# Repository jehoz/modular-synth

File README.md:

# MK-VCO KiCad Project

This repository contains KiCad project files for an **MK-VCO** (Voltage Controlled Oscillator) electronic circuit design.

## Run a KiCad Viewer with Docker

Use the provided Dockerfile and docker-compose.yml to build and run a KiCad environment with VNC and noVNC for web-based access, based on https://hub.docker.com/r/kicad/kicad

```bash
docker-compose up --build
```

- Access the KiCad environment by opening a web browser and navigating to `http://localhost:8080` (VNC password: `kicad`)
    - right click on the desktop, open a terminal, and run:
    ```bash
    kicad /workspace/mk_vco.kicad_pro
    ```

## What is KiCad?

KiCad is free, open-source software for designing electronic circuits and printed circuit boards (PCBs). These files are **not code** in the traditional programming sense—they're design files that describe electronic circuits, components, and PCB layouts.

## File Types Explained

### Project Files (.kicad_pro)
- `mk_vco.kicad_pro` - Main project configuration file
- `mk_vco_JUST_PCB.kicad_pro` - PCB-only version project configuration
- `mk_vco_JUST_PANEL.kicad_pro` - Panel-only version project configuration

These files contain project settings, design rules, and preferences.

### Schematic Files (.kicad_sch)
- `mk_vco.kicad_sch` - Main circuit schematic
- `mk_vco_JUST_PCB.kicad_sch` - PCB-only version schematic

These files contain the electrical circuit diagrams showing how components are connected.

### PCB Layout Files (.kicad_pcb)
- `mk_vco.kicad_pcb` - Main PCB layout
- `mk_vco_JUST_PCB.kicad_pcb` - PCB-only version layout
- `mk_vco_JUST_PANEL.kicad_pcb` - Panel-only version layout

These files define the physical layout of the printed circuit board, including component placement and copper traces.

### Local Settings (.kicad_prl)
- `mk_vco.kicad_prl` - Local project settings
- `mk_vco_JUST_PCB.kicad_prl` - PCB-only local settings

These files store user-specific preferences and window positions (typically not shared in version control).

## Project Variants

This project appears to have three variants:

1. **mk_vco** - Complete project (main version)
2. **mk_vco_JUST_PCB** - PCB-only version (circuit board without panel)
3. **mk_vco_JUST_PANEL** - Panel-only version (front panel design)

## How to Open These Files

1. **Download KiCad**: Get the free software from [https://www.kicad.org/](https://www.kicad.org/)
2. **Install KiCad**: Follow the installation instructions for your operating system
3. **Open Project**: Launch KiCad and open any of the `.kicad_pro` files
4. **View Schematic**: Click "Schematic Editor" to see the circuit diagram
5. **View PCB**: Click "PCB Editor" to see the board layout

## What This Project Is

A **VCO (Voltage Controlled Oscillator)** is an electronic circuit that generates oscillating signals (waveforms) with a frequency that can be controlled by an input voltage. VCOs are commonly used in synthesizers, audio equipment, and other electronic music devices.

## File Format

KiCad files use:
- **JSON** format for project files (.kicad_pro)
- **S-expression** format for schematics (.kicad_sch) and PCB layouts (.kicad_pcb)

These are text-based formats that can be opened in any text editor, but they're best viewed and edited in KiCad.

## Contributing

To modify this project, you'll need to use KiCad's graphical interface rather than editing the files directly. The file formats are complex and contain precise coordinates, component references, and electrical connection data.

## License

[Add your license information here]

---

**Note**: If you're new to electronics design, KiCad has excellent [documentation and tutorials](https://docs.kicad.org/) to help you get started.

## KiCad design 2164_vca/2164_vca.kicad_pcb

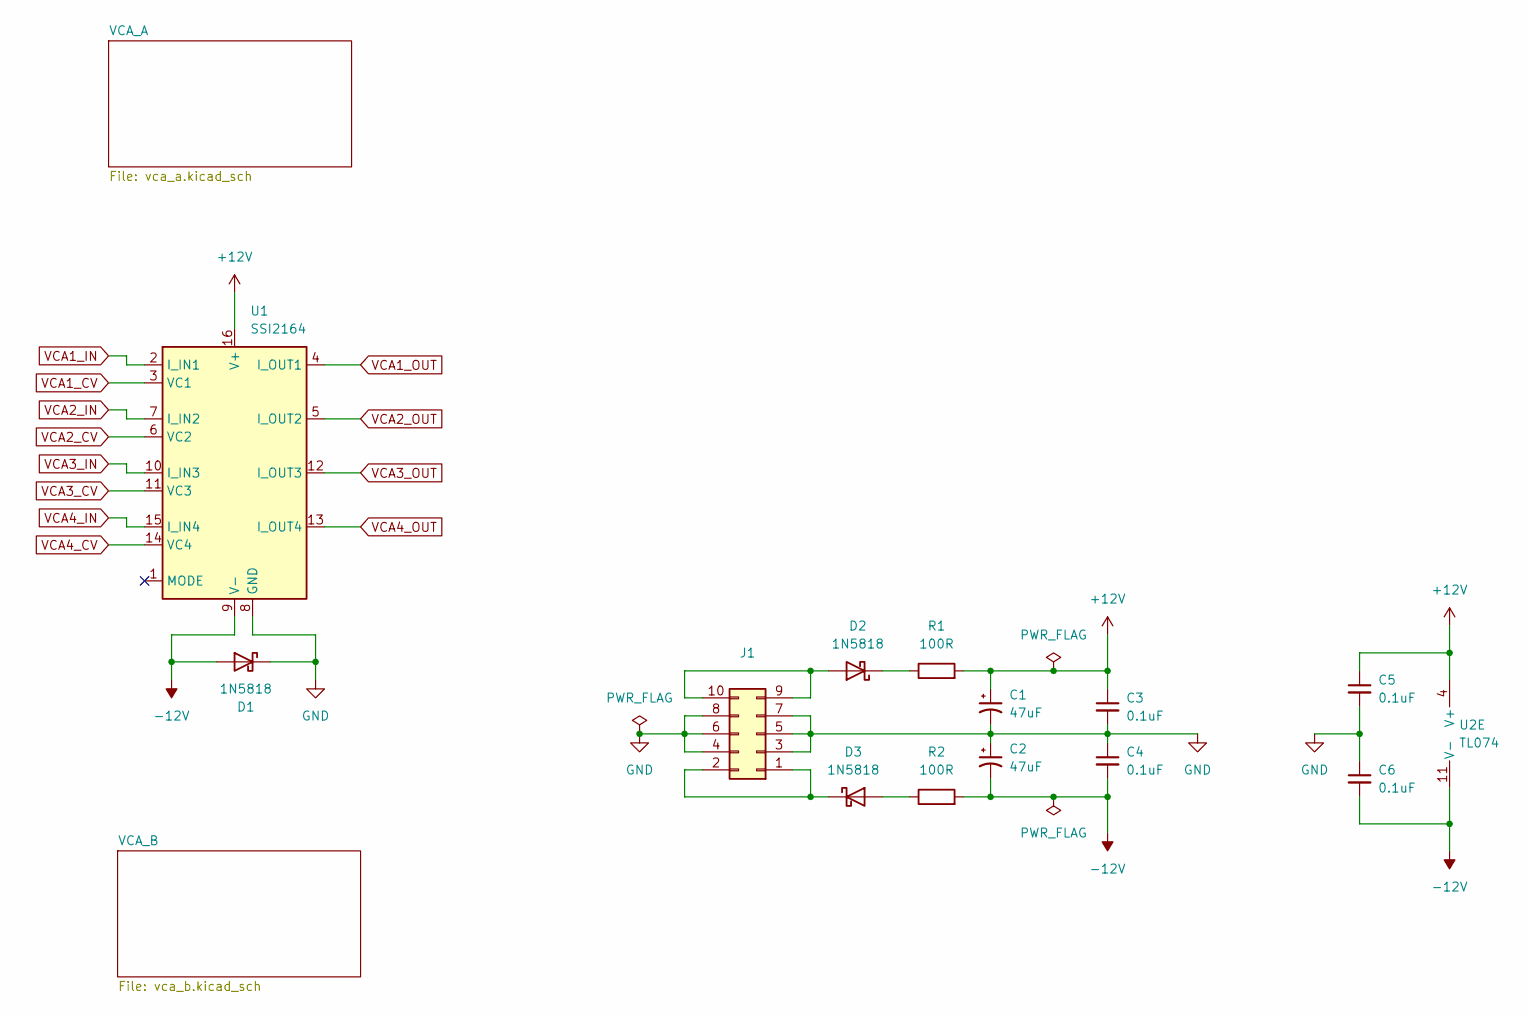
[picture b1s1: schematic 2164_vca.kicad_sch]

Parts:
C1, C2: 47uF; CP_Radial_D6.3mm_P2.50mm
C3, C4, C5, C6: 0.1uF; C_Rect_L7.2mm_W2.5mm_P5.00mm_FKS2_FKP2_MKS2_MKP2
D1, D2, D3: 1N5818; D_DO-41_SOD81_P10.16mm_Horizontal
J1: Power Connector; IDC-Header_2x05_P2.54mm_Vertical
R1, R2: 100R; R_Axial_DIN0207_L6.3mm_D2.5mm_P10.16mm_Horizontal
U1: SSI2164; DIP-16_W7.62mm_Socket
U2: TL074; DIP-14_W7.62mm_Socket

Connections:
+12V: C1.1, C3.1, C5.1, R1.2, U1.16 (V+), U2.4 (V+); also elsewhere on the board
-12V: C2.2, C4.2, C6.2, D1.2 (A), R2.2, U1.9 (V-), U2.11 (V-); also elsewhere on the board
GND: C1.2, C2.1, C3.2, C4.1, C5.2, C6.1, D1.1 (K), J1.3, J1.4, J1.5, J1.6, J1.7, J1.8, U1.8 (GND); also elsewhere on the board
unnamed: D2.2 (A), J1.9, J1.10
unnamed: D2.1 (K), R1.1
unnamed: D3.2 (A), R2.1
unnamed: D3.1 (K), J1.1, J1.2
VCA1_CV: U1.3 (VC1); also elsewhere on the board
VCA1_IN: U1.2 (I_IN1); also elsewhere on the board
VCA1_OUT: U1.4 (I_OUT1); also elsewhere on the board
VCA2_CV: U1.6 (VC2); also elsewhere on the board
VCA2_IN: U1.7 (I_IN2); also elsewhere on the board
VCA2_OUT: U1.5 (I_OUT2); also elsewhere on the board
VCA3_CV: U1.11 (VC3); also elsewhere on the board
VCA3_IN: U1.10 (I_IN3); also elsewhere on the board
VCA3_OUT: U1.12 (I_OUT3); also elsewhere on the board
VCA4_CV: U1.14 (VC4); also elsewhere on the board
VCA4_IN: U1.15 (I_IN4); also elsewhere on the board
VCA4_OUT: U1.13 (I_OUT4); also elsewhere on the board

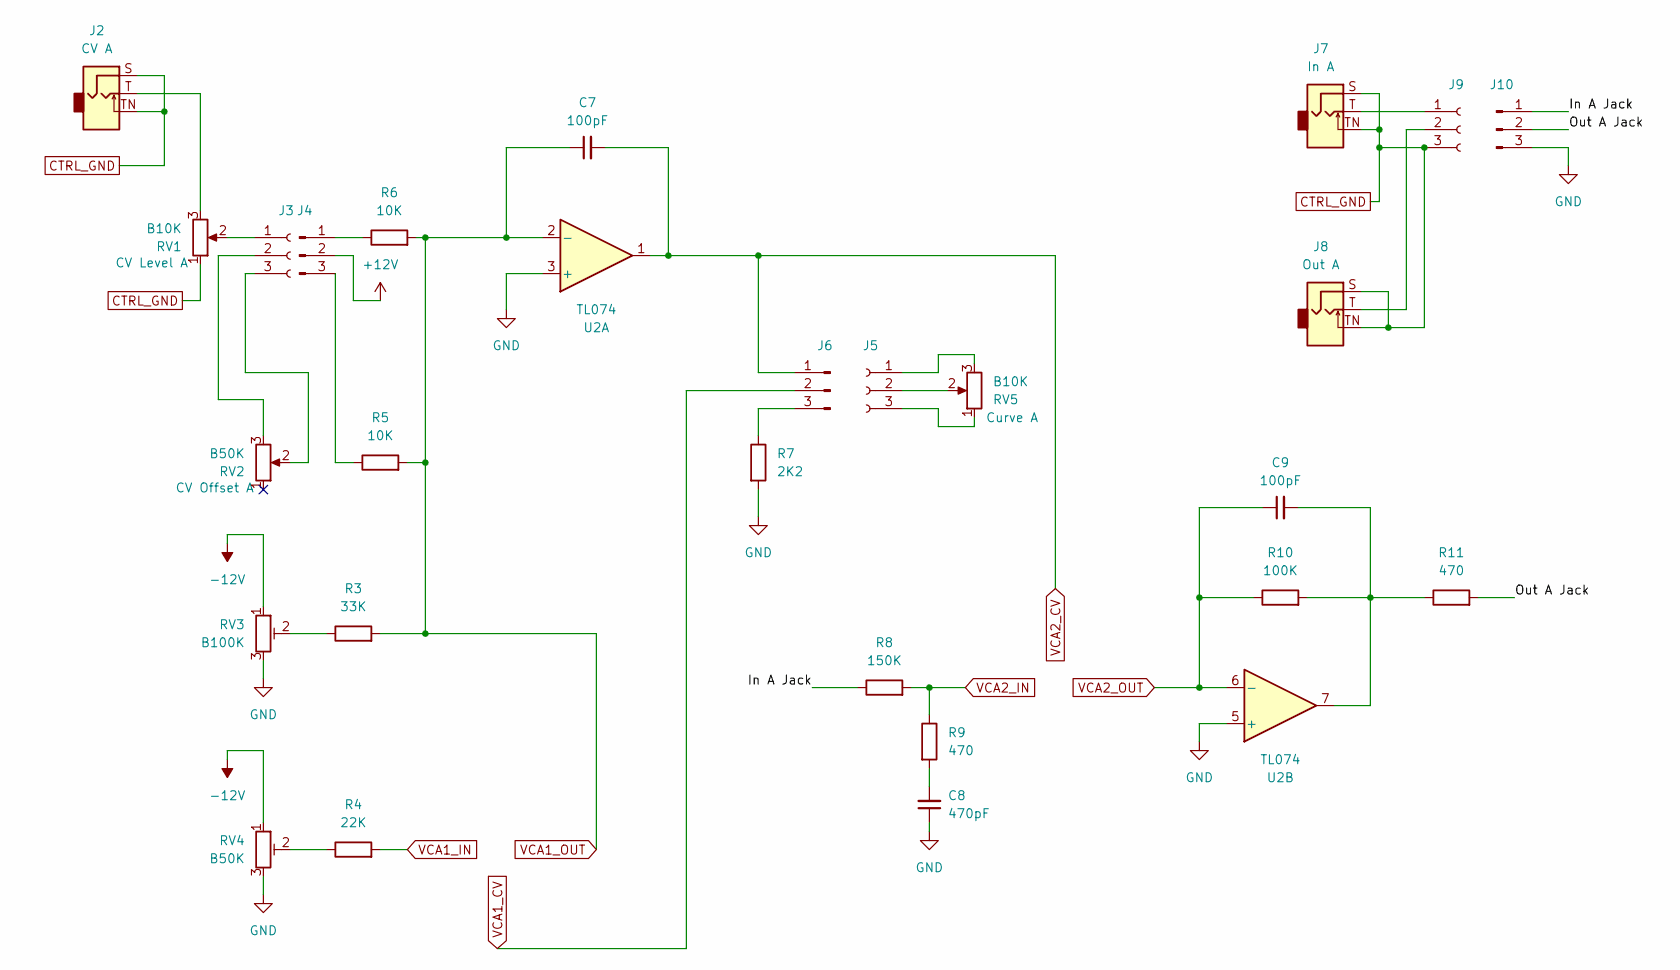
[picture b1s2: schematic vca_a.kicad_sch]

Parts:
C7, C9: 100pF; C_Rect_L7.2mm_W2.5mm_P5.00mm_FKS2_FKP2_MKS2_MKP2
C8: 470pF; C_Rect_L7.2mm_W2.5mm_P5.00mm_FKS2_FKP2_MKS2_MKP2
J2: CV A; Jack_3.5mm_QingPu_WQP-PJ398SM_Vertical_CircularHoles
J3, J5, J9: To J3; PinSocket_1x03_P2.54mm_Vertical
J4, J6, J10: Conn_01x03_Pin; PinHeader_1x03_P2.54mm_Vertical
J7: In A; Jack_3.5mm_QingPu_WQP-PJ398SM_Vertical_CircularHoles
J8: Out A; Jack_3.5mm_QingPu_WQP-PJ398SM_Vertical_CircularHoles
R3: 33K; R_Axial_DIN0207_L6.3mm_D2.5mm_P10.16mm_Horizontal
R4: 22K; R_Axial_DIN0207_L6.3mm_D2.5mm_P10.16mm_Horizontal
R5, R6: 10K; R_Axial_DIN0207_L6.3mm_D2.5mm_P10.16mm_Horizontal
R7: 2K2; R_Axial_DIN0207_L6.3mm_D2.5mm_P10.16mm_Horizontal
R8: 150K; R_Axial_DIN0207_L6.3mm_D2.5mm_P10.16mm_Horizontal
R9, R11: 470; R_Axial_DIN0207_L6.3mm_D2.5mm_P10.16mm_Horizontal
R10: 100K; R_Axial_DIN0207_L6.3mm_D2.5mm_P10.16mm_Horizontal
RV1, RV5: B10K; Potentiometer_Alpha_RD901F-40-00D_Single_Vertical_CircularH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
RV2: B50K; Potentiometer_Alpha_RD901F-40-00D_Single_Vertical_CircularH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
RV3: B100K; Potentiometer_Runtron_RM-065_Vertical
RV4: B50K; Potentiometer_Runtron_RM-065_Vertical
U2: TL074; DIP-14_W7.62mm_Socket

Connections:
+12V: J4.2; also elsewhere on the board
-12V: RV3.1, RV4.1; also elsewhere on the board
/VCA_A/In A Jack: J10.1, R8.1
/VCA_A/Out A Jack: J10.2, R11.2
CTRL_GND: J2.S, J2.TN, J7.S, J7.TN, J8.S, J8.TN, J9.3, RV1.1; also elsewhere on the board
GND: C8.1, J10.3, R7.2, RV3.3, RV4.3, U2.3 (+), U2.5 (+); also elsewhere on the board
unnamed: C8.2, R9.2
unnamed: C9.2, R10.2, R11.1, U2.7
unnamed: J2.T, RV1.3
unnamed: J3.1, RV1.2
unnamed: J3.2, RV2.3
unnamed: J3.3, RV2.2
unnamed: J4.1, R6.1
unnamed: J4.3, R5.1
unnamed: J5.1, RV5.3
unnamed: J5.2, RV5.2
unnamed: J5.3, RV5.1
unnamed: J6.3, R7.1
unnamed: J7.T, J9.1
unnamed: J8.T, J9.2
unnamed: R3.1, RV3.2
unnamed: R4.1, RV4.2
VCA1_CV: J6.2; also elsewhere on the board
VCA1_IN: R4.2; also elsewhere on the board
VCA1_OUT: C7.1, R3.2, R5.2, R6.2, U2.2 (-); also elsewhere on the board
VCA2_CV: C7.2, J6.1, U2.1; also elsewhere on the board
VCA2_IN: R8.2, R9.1; also elsewhere on the board
VCA2_OUT: C9.1, R10.1, U2.6 (-); also elsewhere on the board

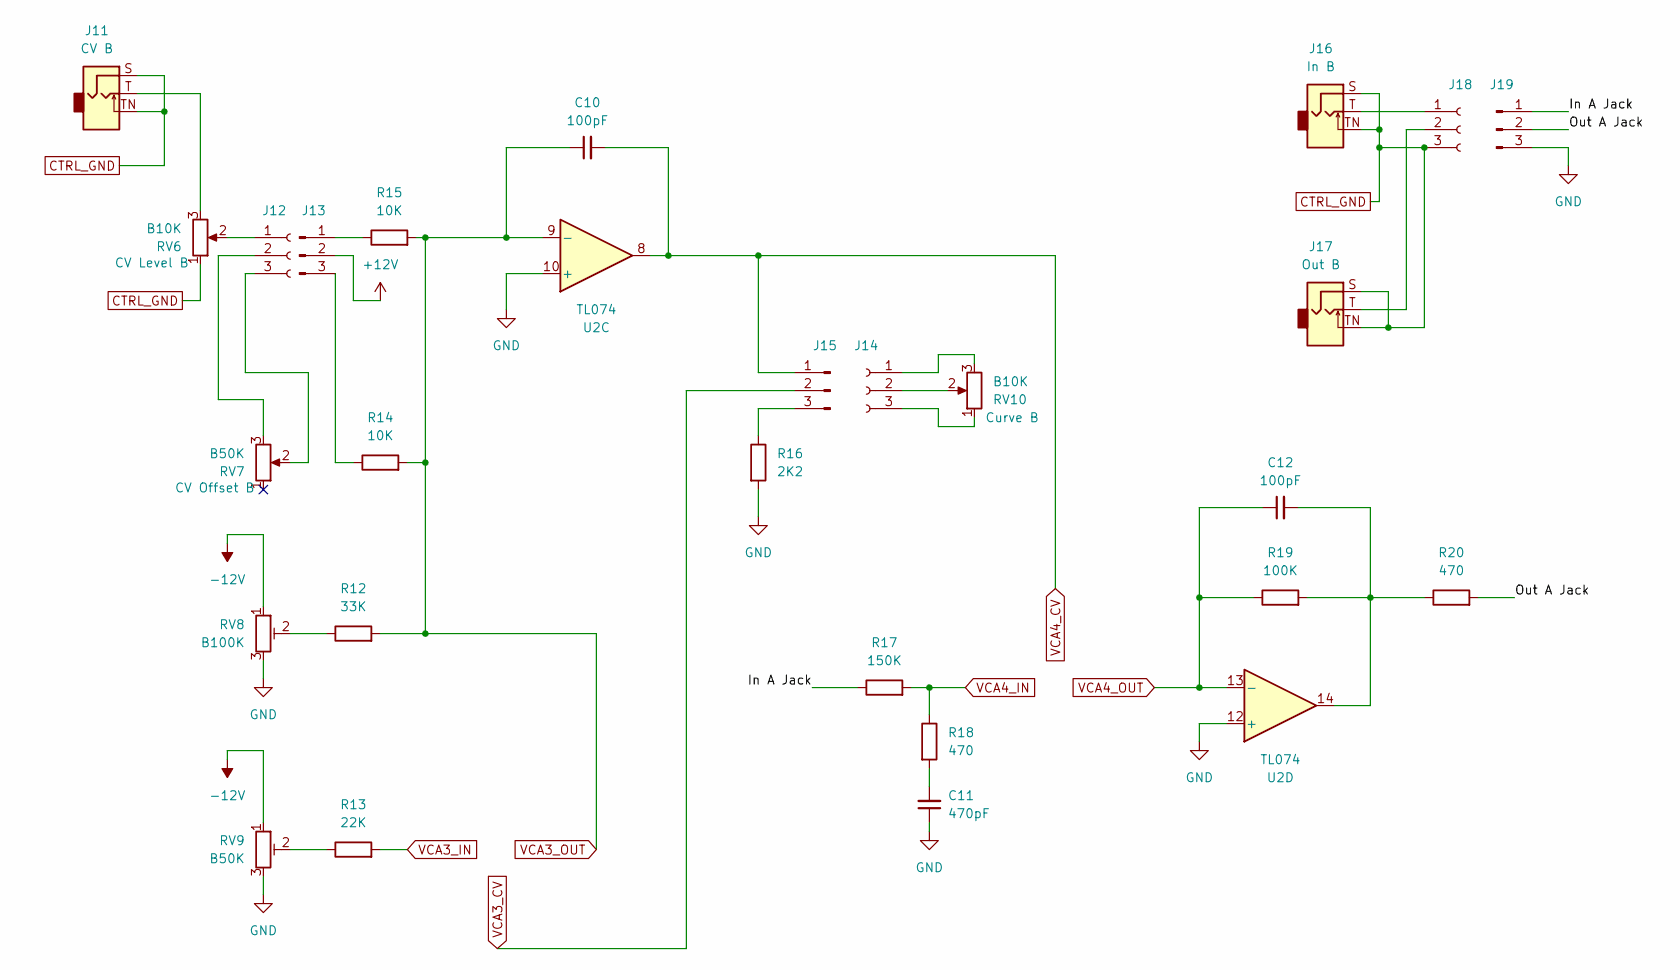
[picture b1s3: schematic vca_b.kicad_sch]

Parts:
C10, C12: 100pF; C_Rect_L7.2mm_W2.5mm_P5.00mm_FKS2_FKP2_MKS2_MKP2
C11: 470pF; C_Rect_L7.2mm_W2.5mm_P5.00mm_FKS2_FKP2_MKS2_MKP2
J11: CV B; Jack_3.5mm_QingPu_WQP-PJ398SM_Vertical_CircularHoles
J12, J14, J18: To J3; PinSocket_1x03_P2.54mm_Vertical
J13, J15, J19: Conn_01x03_Pin; PinHeader_1x03_P2.54mm_Vertical
J16: In B; Jack_3.5mm_QingPu_WQP-PJ398SM_Vertical_CircularHoles
J17: Out B; Jack_3.5mm_QingPu_WQP-PJ398SM_Vertical_CircularHoles
R12: 33K; R_Axial_DIN0207_L6.3mm_D2.5mm_P10.16mm_Horizontal
R13: 22K; R_Axial_DIN0207_L6.3mm_D2.5mm_P10.16mm_Horizontal
R14, R15: 10K; R_Axial_DIN0207_L6.3mm_D2.5mm_P10.16mm_Horizontal
R16: 2K2; R_Axial_DIN0207_L6.3mm_D2.5mm_P10.16mm_Horizontal
R17: 150K; R_Axial_DIN0207_L6.3mm_D2.5mm_P10.16mm_Horizontal
R18, R20: 470; R_Axial_DIN0207_L6.3mm_D2.5mm_P10.16mm_Horizontal
R19: 100K; R_Axial_DIN0207_L6.3mm_D2.5mm_P10.16mm_Horizontal
RV6, RV10: B10K; Potentiometer_Alpha_RD901F-40-00D_Single_Vertical_CircularH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
RV7: B50K; Potentiometer_Alpha_RD901F-40-00D_Single_Vertical_CircularH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
RV8: B100K; Potentiometer_Runtron_RM-065_Vertical
RV9: B50K; Potentiometer_Runtron_RM-065_Vertical
U2: TL074; DIP-14_W7.62mm_Socket

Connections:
+12V: J13.2; also elsewhere on the board
-12V: RV8.1, RV9.1; also elsewhere on the board
/VCA_B/In A Jack: J19.1, R17.1
/VCA_B/Out A Jack: J19.2, R20.2
CTRL_GND: J11.S, J11.TN, J16.S, J16.TN, J17.S, J17.TN, J18.3, RV6.1; also elsewhere on the board
GND: C11.1, J19.3, R16.2, RV8.3, RV9.3, U2.10 (+), U2.12 (+); also elsewhere on the board
unnamed: C11.2, R18.2
unnamed: C12.2, R19.2, R20.1, U2.14
unnamed: J11.T, RV6.3
unnamed: J12.1, RV6.2
unnamed: J12.2, RV7.3
unnamed: J12.3, RV7.2
unnamed: J13.1, R15.1
unnamed: J13.3, R14.1
unnamed: J14.1, RV10.3
unnamed: J14.2, RV10.2
unnamed: J14.3, RV10.1
unnamed: J15.3, R16.1
unnamed: J16.T, J18.1
unnamed: J17.T, J18.2
unnamed: R12.1, RV8.2
unnamed: R13.1, RV9.2
VCA3_CV: J15.2; also elsewhere on the board
VCA3_IN: R13.2; also elsewhere on the board
VCA3_OUT: C10.1, R12.2, R14.2, R15.2, U2.9 (-); also elsewhere on the board
VCA4_CV: C10.2, J15.1, U2.8; also elsewhere on the board
VCA4_IN: R17.2, R18.1; also elsewhere on the board
VCA4_OUT: C12.1, R19.1, U2.13 (-); also elsewhere on the board

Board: 2 copper layers, 66 parts (13 on the bottom side), 56 nets, no tracks yet.

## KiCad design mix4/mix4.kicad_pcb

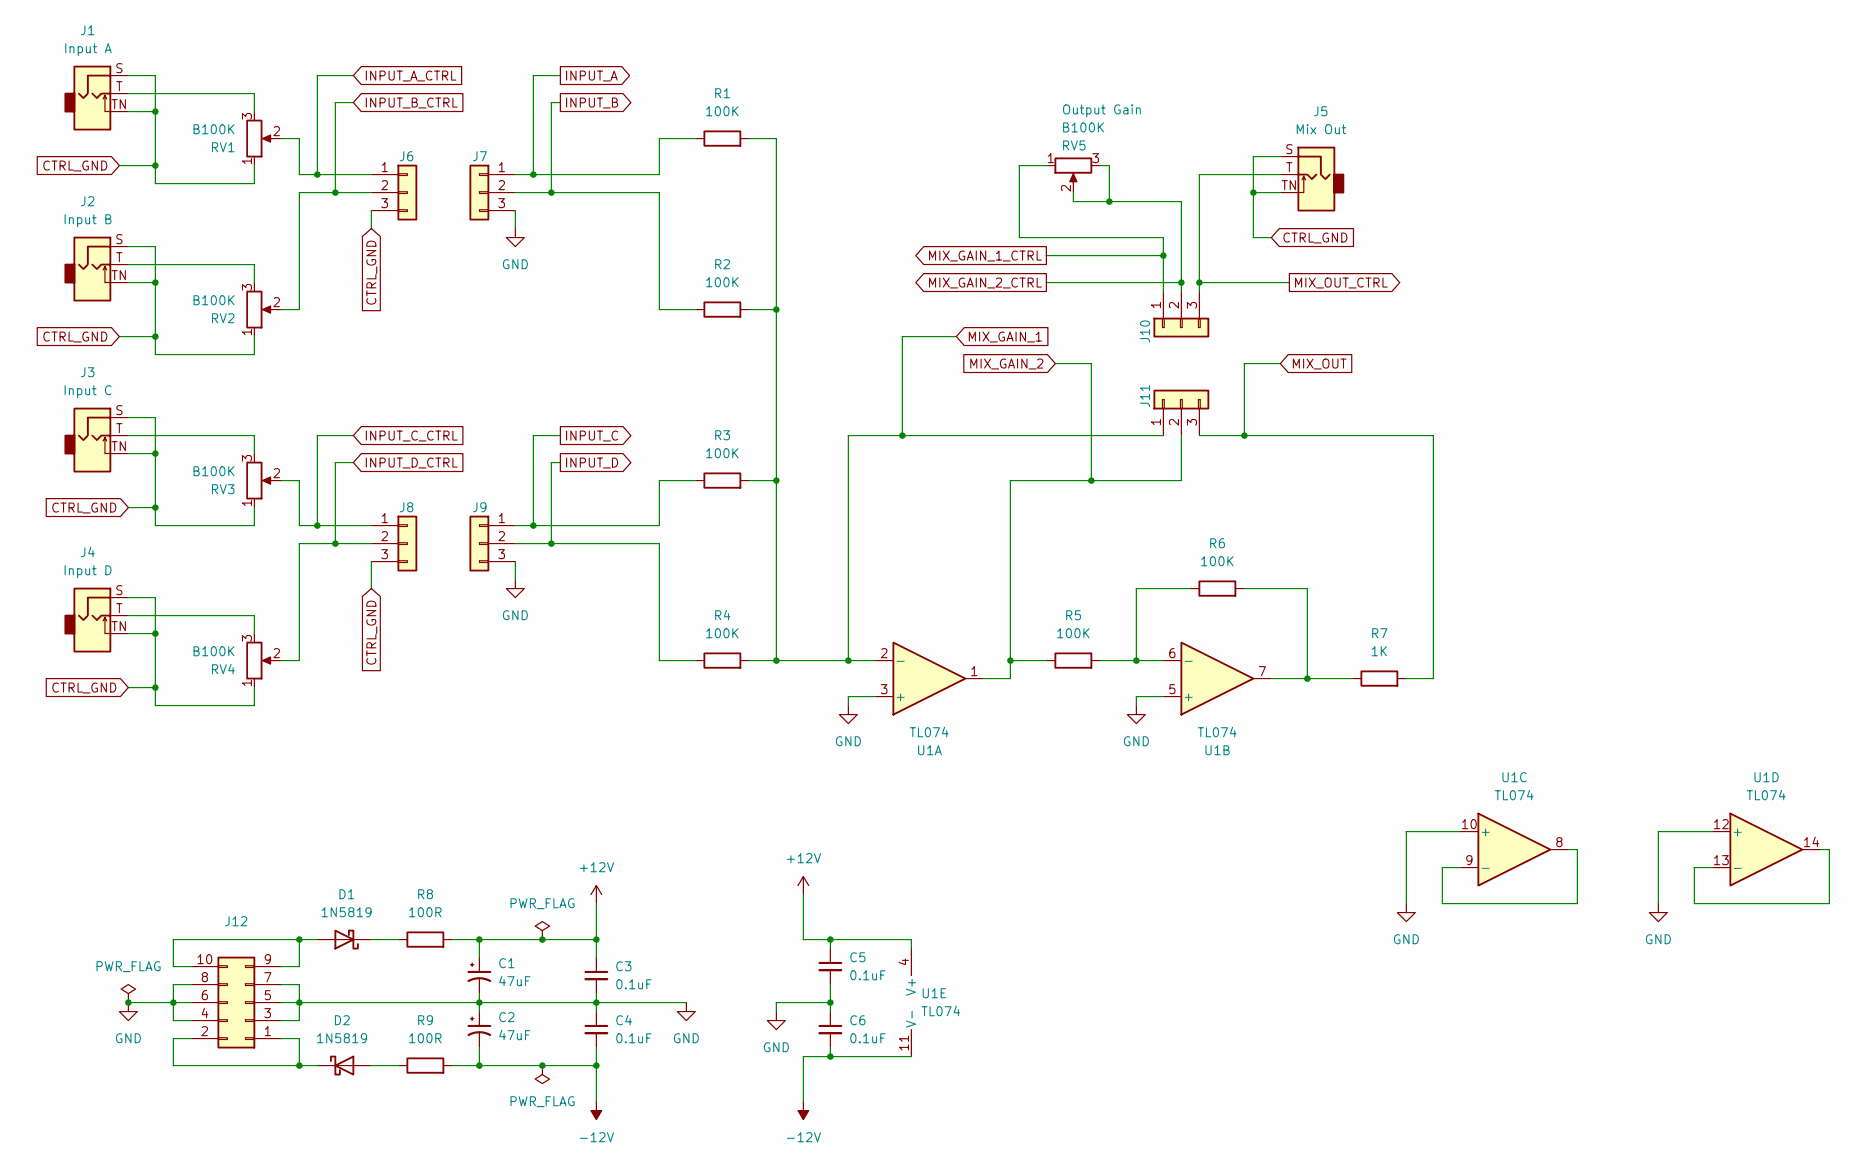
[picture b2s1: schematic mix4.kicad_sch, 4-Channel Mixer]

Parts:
C1, C2: 47uF; CP_Radial_D6.3mm_P2.50mm
C3, C4, C5, C6: 0.1uF; C_Rect_L7.2mm_W2.5mm_P5.00mm_FKS2_FKP2_MKS2_MKP2
D1, D2: 1N5819; D_DO-41_SOD81_P10.16mm_Horizontal
J1: Input A; Jack_3.5mm_QingPu_WQP-PJ398SM_Vertical_CircularHoles
J2: Input B; Jack_3.5mm_QingPu_WQP-PJ398SM_Vertical_CircularHoles
J3: Input C; Jack_3.5mm_QingPu_WQP-PJ398SM_Vertical_CircularHoles
J4: Input D; Jack_3.5mm_QingPu_WQP-PJ398SM_Vertical_CircularHoles
J5: Mix Out; Jack_3.5mm_QingPu_WQP-PJ398SM_Vertical_CircularHoles
J6, J8: Conn_01x03; PinHeader_1x03_P2.54mm_Vertical
J7, J9: PinSocket_1x03_P2.54mm_Vertical
J10: PinHeader_1x03_P2.54mm_Vertical
J11: Conn_01x03; PinSocket_1x03_P2.54mm_Vertical
J12: Power Connector; IDC-Header_2x05_P2.54mm_Vertical
R1, R2, R3, R4, R5, R6: 100K; R_Axial_DIN0207_L6.3mm_D2.5mm_P10.16mm_Horizontal
R7: 1K; R_Axial_DIN0207_L6.3mm_D2.5mm_P10.16mm_Horizontal
R8, R9: 100R; R_Axial_DIN0207_L6.3mm_D2.5mm_P10.16mm_Horizontal
RV1, RV2, RV3, RV4, RV5: B100K; Potentiometer_Alpha_RD901F-40-00D_Single_Vertical_CircularH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
U1: TL074; DIP-14_W7.62mm_Socket

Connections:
+12V: C1.1, C3.1, C5.1, R8.2, U1.4 (V+)
-12V: C2.2, C4.2, C6.2, R9.2, U1.11 (V-)
CTRL_GND: J1.S, J1.TN, J2.S, J2.TN, J3.S, J3.TN, J4.S, J4.TN, J5.S, J5.TN, J6.3, J8.3, RV1.1, RV2.1, RV3.1, RV4.1
GND: C1.2, C2.1, C3.2, C4.1, C5.2, C6.1, J7.3, J9.3, J12.3, J12.4, J12.5, J12.6, J12.7, J12.8, U1.3 (+), U1.5 (+), U1.10 (+), U1.12 (+)
INPUT_A: J7.1, R1.1
INPUT_A_CTRL: J6.1, RV1.2
INPUT_B: J7.2, R2.1
INPUT_B_CTRL: J6.2, RV2.2
INPUT_C: J9.1, R3.1
INPUT_C_CTRL: J8.1, RV3.2
INPUT_D: J9.2, R4.1
INPUT_D_CTRL: J8.2, RV4.2
MIX_GAIN_1: J11.1, R1.2, R2.2, R3.2, R4.2, U1.2 (-)
MIX_GAIN_1_CTRL: J10.1, RV5.1
MIX_GAIN_2: J11.2, R5.1, U1.1
MIX_GAIN_2_CTRL: J10.2, RV5.2, RV5.3
MIX_OUT: J11.3, R7.2
MIX_OUT_CTRL: J5.T, J10.3
unnamed: D1.2 (A), J12.9, J12.10
unnamed: D1.1 (K), R8.1
unnamed: D2.2 (A), R9.1
unnamed: D2.1 (K), J12.1, J12.2
unnamed: J1.T, RV1.3
unnamed: J2.T, RV2.3
unnamed: J3.T, RV3.3
unnamed: J4.T, RV4.3
unnamed: R6.2, R7.1, U1.7
unnamed: R5.2, R6.1, U1.6 (-)
unnamed: U1.8, U1.9 (-)
unnamed: U1.13 (-), U1.14

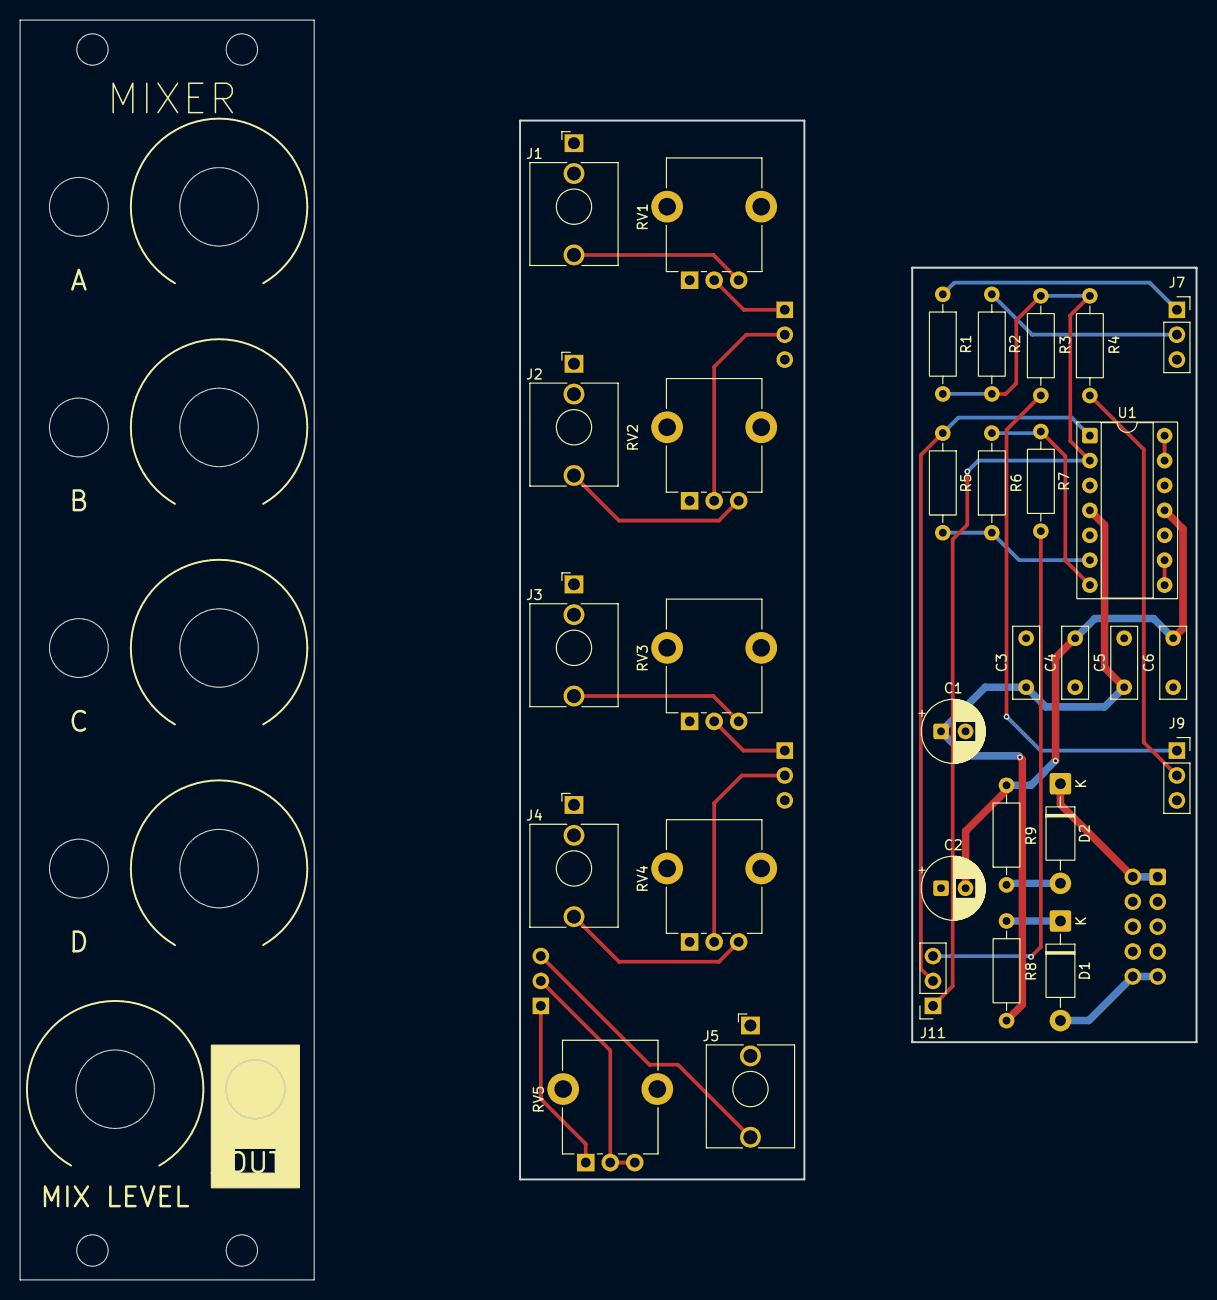
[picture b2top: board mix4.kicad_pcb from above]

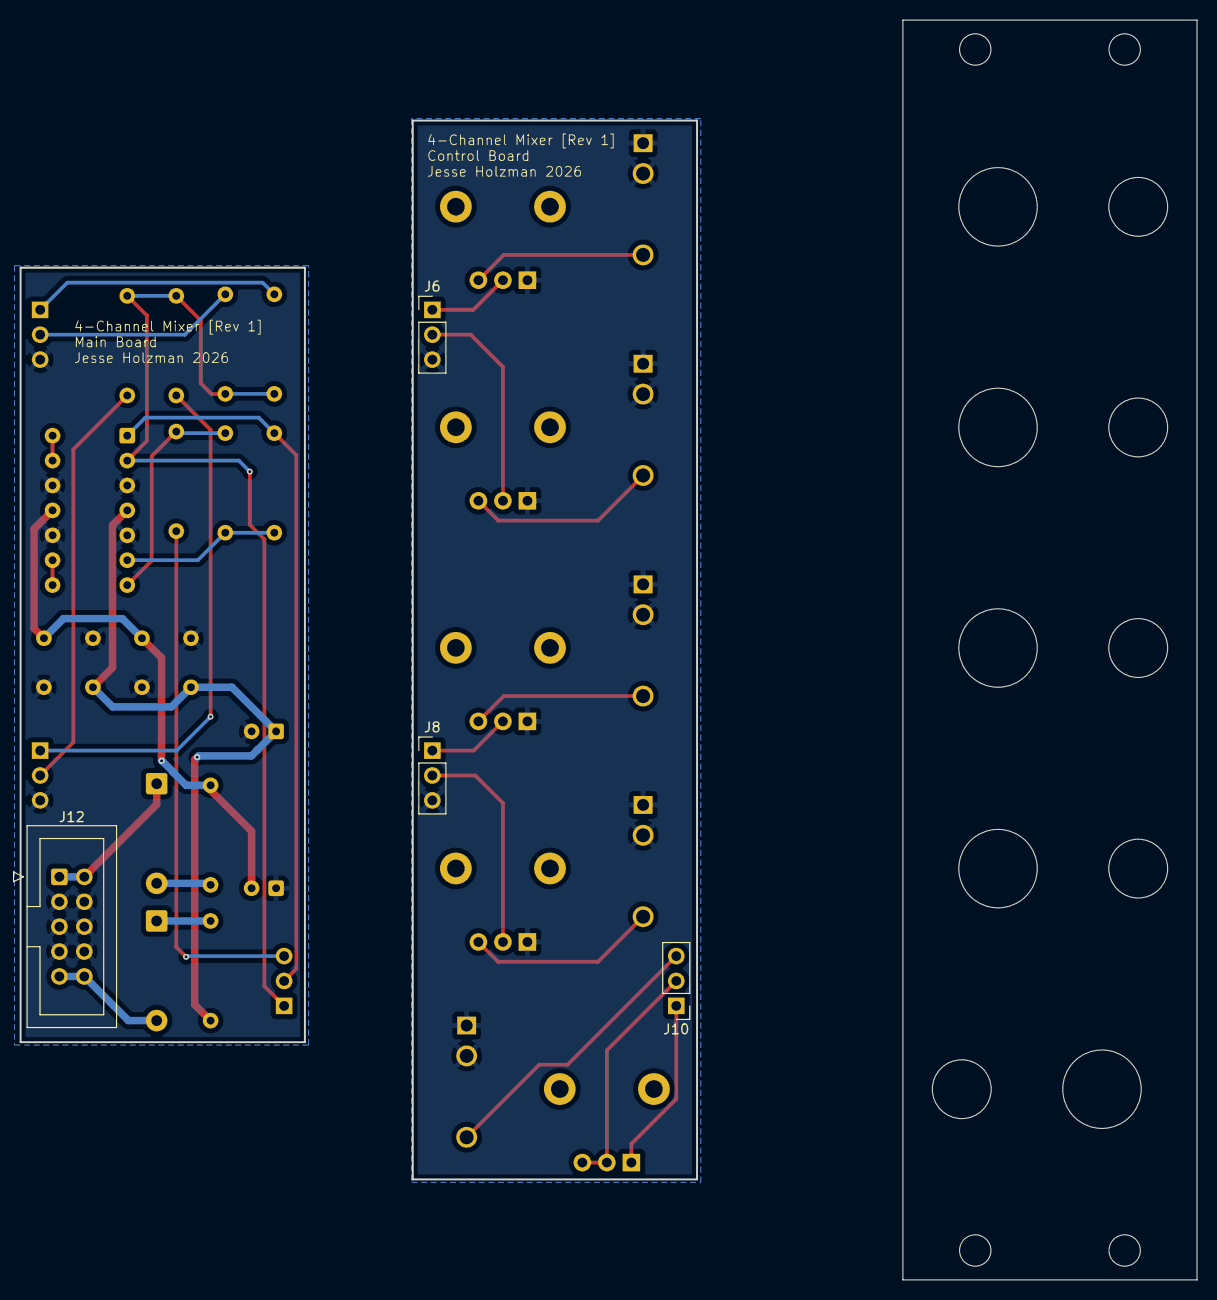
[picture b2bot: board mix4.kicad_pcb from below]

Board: 2 copper layers, 119.9 x 128.4 mm, 35 parts (4 on the bottom side), 30 nets.

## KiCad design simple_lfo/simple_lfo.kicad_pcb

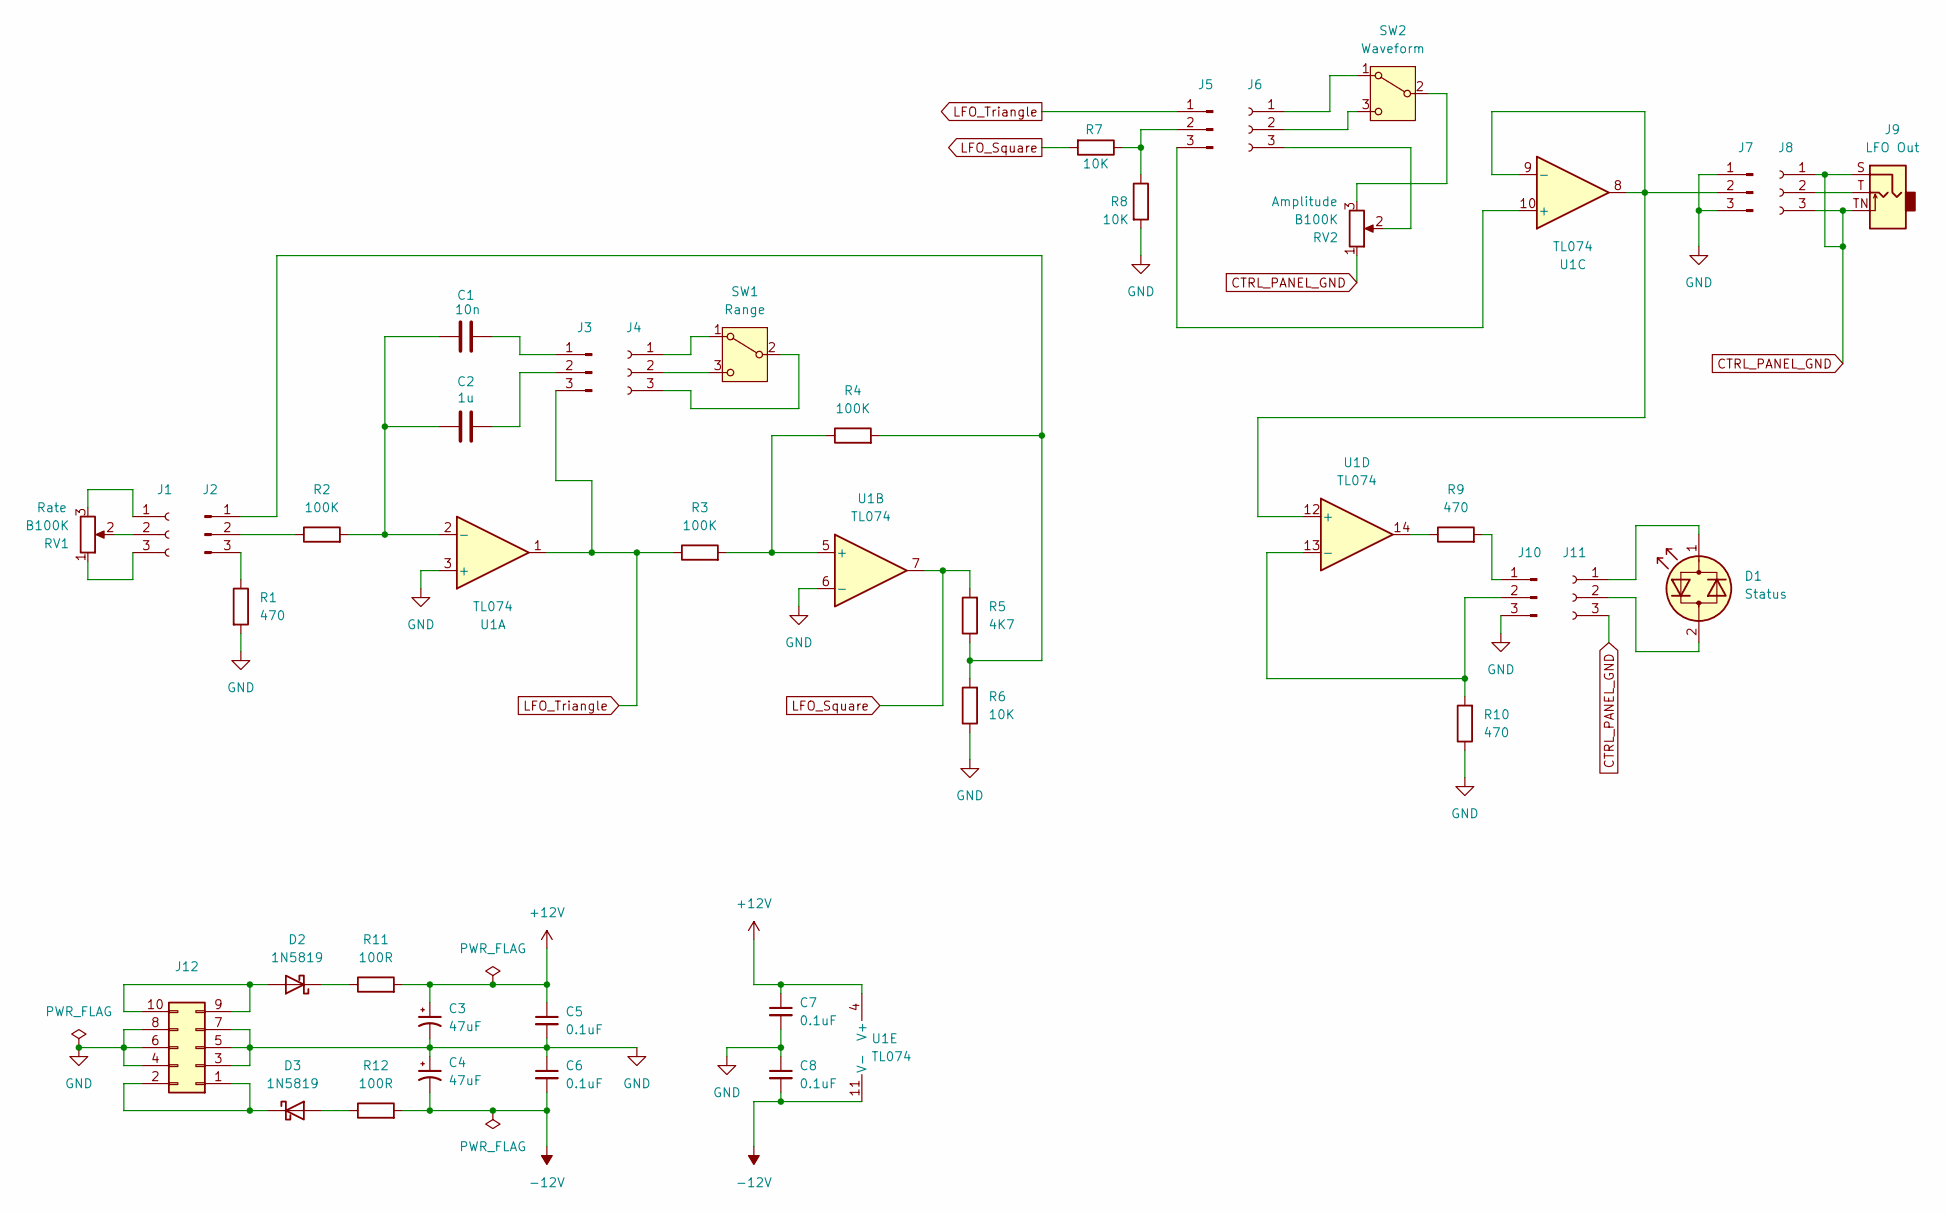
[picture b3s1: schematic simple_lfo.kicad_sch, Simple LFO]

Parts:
C1: 10n; C_Rect_L7.2mm_W2.5mm_P5.00mm_FKS2_FKP2_MKS2_MKP2
C2: 1u; C_Rect_L7.0mm_W6.0mm_P5.00mm
C3, C4: 47uF; CP_Radial_D6.3mm_P2.50mm
C5, C6, C7, C8: 0.1uF; C_Rect_L7.2mm_W2.5mm_P5.00mm_FKS2_FKP2_MKS2_MKP2
D1: Status; LED_D3.0mm
D2, D3: 1N5819; D_DO-41_SOD81_P10.16mm_Horizontal
J1, J4, J6, J8, J11: To J3; PinSocket_1x03_P2.54mm_Vertical
J2: Conn_01x03_Pin; PinHeader_1x03_P2.54mm_Vertical
J3, J5, J7, J10: To J4 (Range Switch); PinHeader_1x03_P2.54mm_Vertical
J9: LFO Out; Jack_3.5mm_QingPu_WQP-PJ398SM_Vertical_CircularHoles
J12: Power Connector; IDC-Header_2x05_P2.54mm_Vertical
R1, R9, R10: 470; R_Axial_DIN0207_L6.3mm_D2.5mm_P10.16mm_Horizontal
R2, R3, R4: 100K; R_Axial_DIN0207_L6.3mm_D2.5mm_P10.16mm_Horizontal
R5: 4K7; R_Axial_DIN0207_L6.3mm_D2.5mm_P10.16mm_Horizontal
R6, R7, R8: 10K; R_Axial_DIN0207_L6.3mm_D2.5mm_P10.16mm_Horizontal
R11, R12: 100R; R_Axial_DIN0207_L6.3mm_D2.5mm_P10.16mm_Horizontal
RV1, RV2: B100K; Potentiometer_Alpha_RD901F-40-00D_Single_Vertical_CircularH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
SW1: Range; PinHeader_1x03_P2.54mm_Vertical
SW2: Waveform; PinHeader_1x03_P2.54mm_Vertical
U1: TL074; DIP-14_W7.62mm_Socket

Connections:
+12V: C3.1, C5.1, C7.1, R11.2, U1.4 (V+)
-12V: C4.2, C6.2, C8.2, R12.2, U1.11 (V-)
CTRL_PANEL_GND: J8.1, J8.3, J9.S, J9.TN, J11.3, RV2.1
GND: C3.2, C4.1, C5.2, C6.1, C7.2, C8.1, J7.1, J7.3, J10.3, J12.3, J12.4, J12.5, J12.6, J12.7, J12.8, R1.2, R6.1, R8.2, R10.1, U1.3 (+), U1.6 (-)
LFO_Square: R5.2, R7.2, U1.7
LFO_Triangle: J3.3, J5.1, R3.1, U1.1
unnamed: D1.2 (AK), J11.2
unnamed: D1.1 (KA), J11.1
unnamed: D2.2 (A), J12.9, J12.10
unnamed: D2.1 (K), R11.1
unnamed: D3.2 (A), R12.1
unnamed: D3.1 (K), J12.1, J12.2
unnamed: J1.1, RV1.3
unnamed: J1.2, RV1.2
unnamed: J1.3, RV1.1
unnamed: J2.1, R4.2, R5.1, R6.2
unnamed: J2.2, R2.1
unnamed: J2.3, R1.1
unnamed: C1.2, J3.1
unnamed: C2.2, J3.2
unnamed: J4.1, SW1.1 (A)
unnamed: J4.2, SW1.3 (C)
unnamed: J4.3, SW1.2 (B)
unnamed: J5.2, R7.1, R8.1
unnamed: J5.3, U1.10 (+)
unnamed: J6.1, SW2.1 (A)
unnamed: J6.2, SW2.3 (C)
unnamed: J6.3, RV2.2
unnamed: J7.2, U1.8, U1.9 (-), U1.12 (+)
unnamed: J8.2, J9.T
unnamed: J10.1, R9.2
unnamed: J10.2, R10.2, U1.13 (-)
unnamed: R9.1, U1.14
unnamed: RV2.3, SW2.2 (B)
unnamed: C1.1, C2.1, R2.2, U1.2 (-)
unnamed: R3.2, R4.1, U1.5 (+)

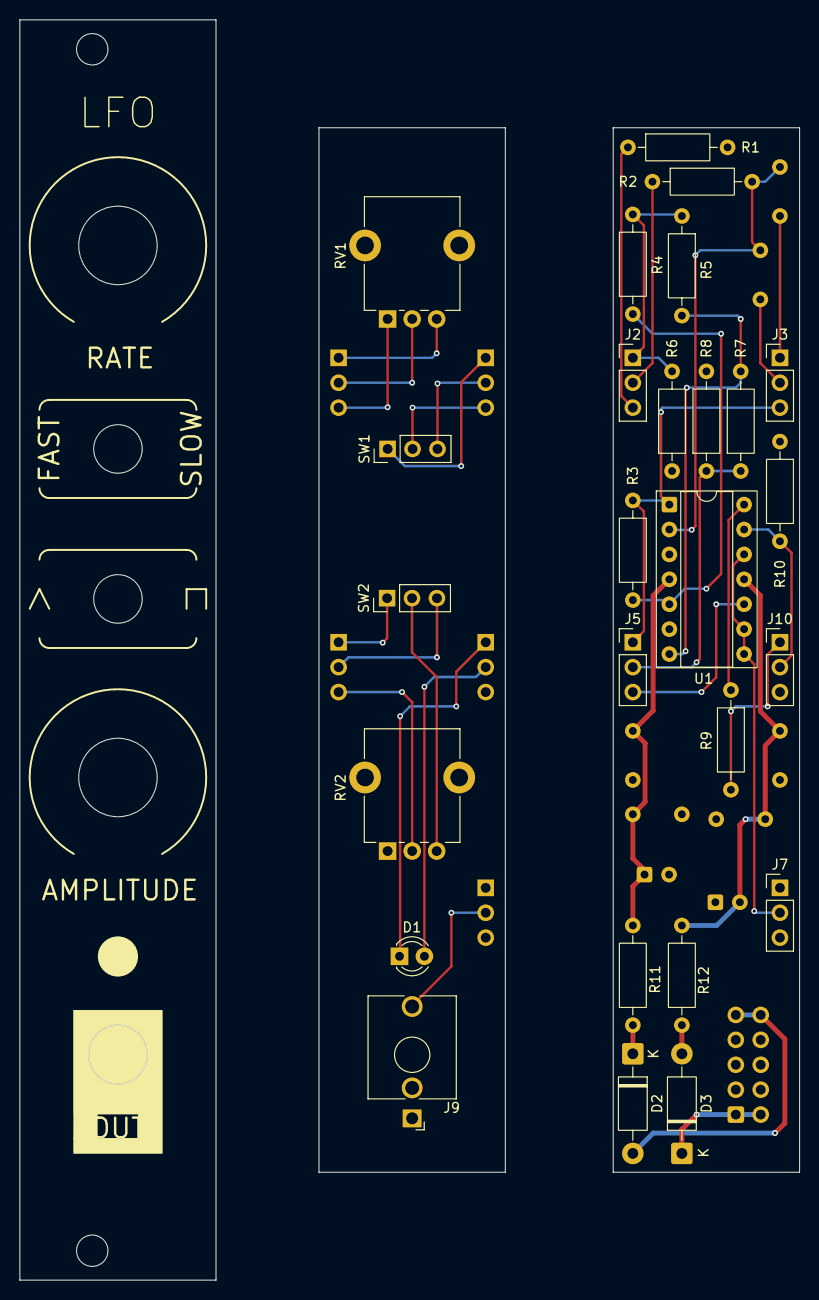
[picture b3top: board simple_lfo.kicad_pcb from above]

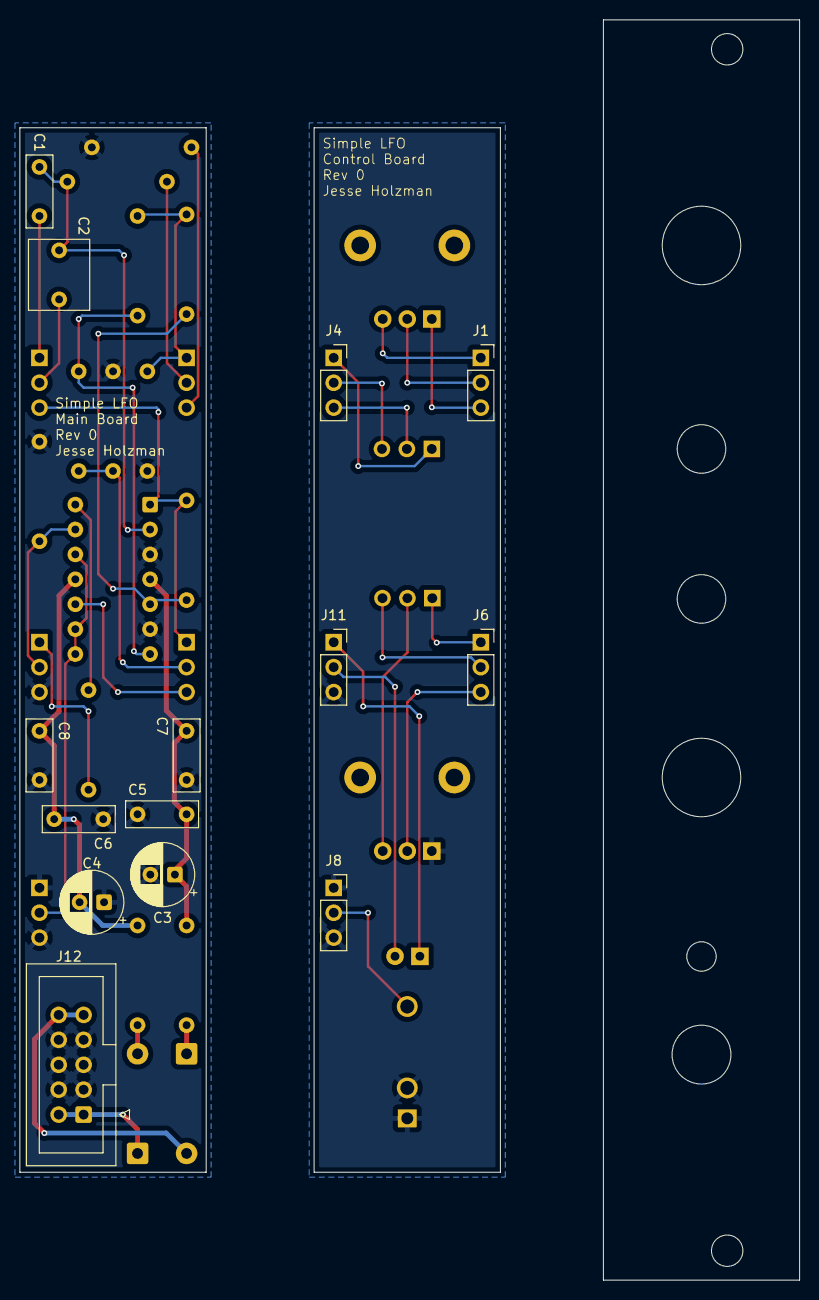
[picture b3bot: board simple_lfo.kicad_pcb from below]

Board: 2 copper layers, 79.5 x 128.5 mm, 40 parts (14 on the bottom side), 36 nets.
